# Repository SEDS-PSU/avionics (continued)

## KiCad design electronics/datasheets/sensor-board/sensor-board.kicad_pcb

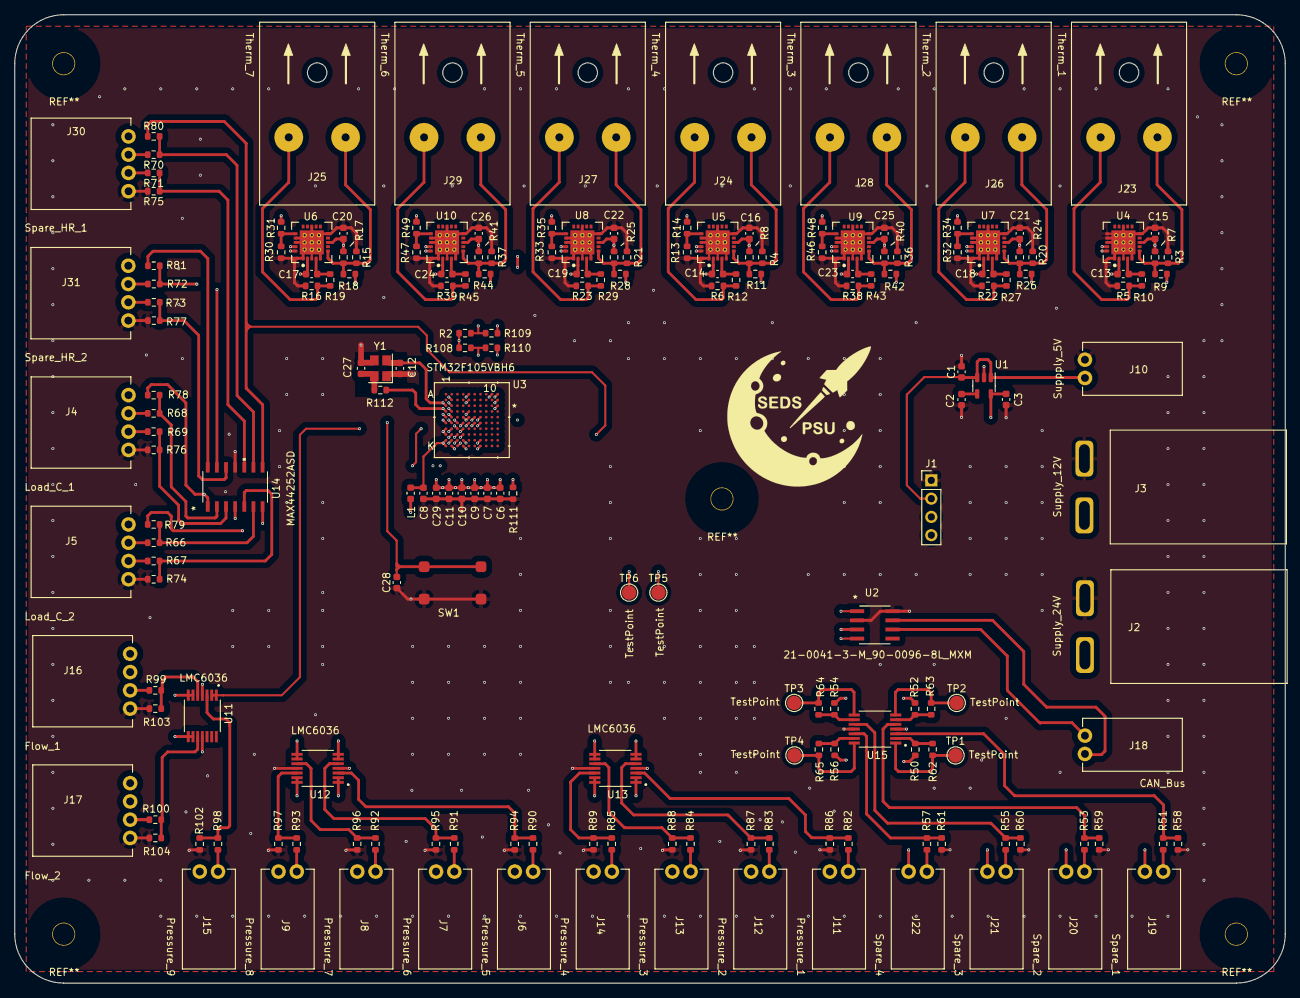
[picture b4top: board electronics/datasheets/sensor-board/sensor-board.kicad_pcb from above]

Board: 4 copper layers, 176.6 x 134.6 mm, 190 parts (0 on the bottom side), 131 nets.

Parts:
C1, C3: 1uF; C_0603_1608Metric
C2: 10nF; C_0603_1608Metric
C6, C7, C8, C9, C10, C11, C28, C29: 100nF; C_0603_1608Metric
C12, C27: 20pF; C_0603_1608Metric
C13, C14, C15, C16, C17, C18, C19, C20, C21, C22, C23, C24, C25, C26: 0.1uF; C_0603_1608Metric
J1: SWD Header; PinHeader_1x04_P2.54mm_Vertical
J2: Supply_24V; PowerPoleThroughHole
J3: Supply_12V; PowerPoleThroughHole
J4: Load_C_1; SL_2.54_H_4pin
J5: Load_C_2; SL_2.54_H_4pin
J6: Pressure_5; SL_2.54_H_2pin
J7: Pressure_6; SL_2.54_H_2pin
J8: Pressure_7; SL_2.54_H_2pin
J9: Pressure_8; SL_2.54_H_2pin
J10: Suppply_5V; SL_2.54_H_2pin
J11: Pressure_1; SL_2.54_H_2pin
J12: Pressure_2; SL_2.54_H_2pin
J13: Pressure_3; SL_2.54_H_2pin
J14: Pressure_4; SL_2.54_H_2pin
J15: Pressure_9; SL_2.54_H_2pin
J16: Flow_1; SL_2.54_H_4pin
J17: Flow_2; SL_2.54_H_4pin
J18: CAN_Bus; SL_2.54_H_2pin
J19: Spare_1; SL_2.54_H_2pin
J20: Spare_2; SL_2.54_H_2pin
J21: Spare_3; SL_2.54_H_2pin
J22: Spare_4; SL_2.54_H_2pin
J23: Therm_1; K_type_thermo_conn_F
J24: Therm_4; K_type_thermo_conn_F
J25: Therm_7; K_type_thermo_conn_F
J26: Therm_2; K_type_thermo_conn_F
J27: Therm_5; K_type_thermo_conn_F
J28: Therm_3; K_type_thermo_conn_F
J29: Therm_6; K_type_thermo_conn_F
J30: Spare_HR_1; SL_2.54_H_4pin
J31: Spare_HR_2; SL_2.54_H_4pin
L1: 10uH; L_0603_1608Metric
R2, R108: 4.7k; R_0603_1608Metric
R3, R4, R5, R6, R15, R16, R20, R21, R22, R23, R36, R37, R38, R39: 2M; R_0603_1608Metric
R7, R8, R17, R24, R25, R40, R41: 1M; R_0603_1608Metric
R9, R10, R11, R12, R18, R19, R26, R27, R28, R29, R42, R43, R44, R45, R66, R68, R70, R72, R109, R110: 100; R_0603_1608Metric
R13, R30, R32, R33, R46, R47, R111: 10k; R_0603_1608Metric
R14: 7.5k; R_0603_1608Metric
R31: 43k; R_0603_1608Metric
R34: 2.2k; R_0603_1608Metric
R35: 13k; R_0603_1608Metric
R48: 4.3k; R_0603_1608Metric
R49: 22k; R_0603_1608Metric
R50, R51, R52, R53, R54, R55, R56, R57, R58, R59, R60, R61, R62, R63, R64, R65: NO_RES; R_0603_1608Metric
R67, R69, R71, R73: 24.92; R_0603_1608Metric
R74, R75, R76, R77, R78, R79, R80, R81: 82500; R_0603_1608Metric
R82, R83, R84, R85, R86, R87, R88, R89, R90, R91, R92, R93, R94, R95, R96, R97, R98, R99, R100, R102, R103, R104: 150; R_0603_1608Metric
R112: 0k; R_0603_1608Metric
Ref**: Val**; seds-logo
SW1: SW_Push_Dual; Button CS1102
TP1, TP2, TP3, TP4, TP5, TP6: TestPoint; TestPoint_Pad_D2.0mm
U1: LD3985M33R_SOT23; SOT-23-5
U2: 21-0041-3-M_90-0096-8L_MXM; MAX33012EASA+
U3: STM32F105VBH6
U4, U5, U6, U7, U8, U9, U10: MCP96RL01T; MCP96RL01T_QFN
U11, U12, U13, U15: LMC6036; SOP65P640X120-14N
U14: MAX44252ASD; MAX44252ASD&plus_
Y1: Crystal_GND24; Crystal_SMD_3225-4Pin_3.2x2.5mm

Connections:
+3V3: C3.1, C6.1, C7.1, C9.1, C10.1, C11.1, C15.1, C16.1, C20.1, C21.1, C22.1, C25.1, C26.1, C29.1, L1.2, R2.1, R7.1, R8.1, R14.2, R17.1, R24.1, R25.1, R31.2, R34.2, R35.2, R40.1, R41.1, R48.2, R49.2, R108.1, U1.5 (VOUT), U2.3 (VDD), U3.B2 (VBAT), U3.D2 (VDD_5), U3.F4 (VDD_4), U3.F5 (VDD_3), U3.F6 (VDD_2), U3.F7 (VDD_1), U4.8 (VDD), U5.8 (VDD), U6.8 (VDD), U7.8 (VDD), U8.8 (VDD), U9.8 (VDD), U10.8 (VDD), U11.4 (VDD), U12.4 (VDD), U13.4 (VDD), U14.4 (VDD), U15.4 (VDD)
+5V: C1.1, J1.2, J10.1, U1.1 (VIN), U1.3 (INH)
+12V: J3.1, J4.1, J5.1, J6.1, J7.1, J8.1, J9.1, J11.1, J12.1, J13.1, J14.1, J15.1, J30.1, J31.1
+24V: J2.1, J16.1, J17.1
/ADC12_IN0: R78.1, U3.G2 (PA0-WKUP), U14.1 (OUTA)
/ADC12_IN1: R79.1, U3.H2 (PA1), U14.7 (OUTB)
/ADC12_IN2: U3.J2 (PA2), U12.8 (OUTC), U12.9 (INC-)
/ADC12_IN3: U3.K2 (PA3), U12.13 (IND-), U12.14 (OUTD)
/ADC12_IN4: U3.G3 (PA4), U12.1 (OUTA), U12.2 (INA-)
/ADC12_IN5: U3.H3 (PA5), U12.6 (INB-), U12.7 (OUTB)
/ADC12_IN6: U3.J3 (PA6), U13.1 (OUTA), U13.2 (INA-)
/ADC12_IN7: U3.K3 (PA7), U13.6 (INB-), U13.7 (OUTB)
/ADC12_IN8: U3.J4 (PB0), U13.8 (OUTC), U13.9 (INC-)
/ADC12_IN9: U3.K4 (PB1), U13.13 (IND-), U13.14 (OUTD)
/ADC12_IN10: U3.F1 (PC0), U11.1 (OUTA), U11.2 (INA-)
/ADC12_IN11: U3.F2 (PC1), U11.6 (INB-), U11.7 (OUTB)
/ADC12_IN12: U3.E2 (PC2), U11.8 (OUTC), U11.9 (INC-)
/ADC12_IN13: TP5.1, U3.F3 (PC3)
/ADC12_IN14: TP6.1, U3.G4 (PC4)
/ADC12_IN15: R80.1, U3.H4 (PC5), U14.8 (OUTC)
/CAN_RX: U2.4 (RXD), U3.C10 (PA11)
/CAN_TX: U2.1 (TXD), U3.B10 (PA12)
/I2C1_SCL: R2.2, R109.1, U4.19 (SCL), U5.19 (SCL), U6.19 (SCL), U7.19 (SCL), U8.19 (SCL), U9.19 (SCL), U10.19 (SCL)
/I2C1_SDA: R108.2, R110.1, U4.20 (SDA), U5.20 (SDA), U6.20 (SDA), U7.20 (SDA), U8.20 (SDA), U9.20 (SDA), U10.20 (SDA)
/Load Cell/diff+A: J4.3, R69.2
/Load Cell/diff+B: J5.3, R67.2
/Load Cell/diff+C: J30.3, R71.2
/Load Cell/diff+D: J31.3, R73.2
/Load Cell/diff-A: J4.2, R68.2
/Load Cell/diff-B: J5.2, R66.2
/Load Cell/diff-C: J30.2, R70.2
/Load Cell/diff-D: J31.2, R72.2
/Load Cell/output_D: R81.1, U14.14 (OUTD)
/Pressure 1/diff+A: J11.2, R82.2
/Pressure 1/diff+B: J12.2, R83.2
/Pressure 1/diff+C: J13.2, R84.2
/Pressure 1/diff+D: J14.2, R85.2
/Pressure 2/diff+A: J6.2, R90.2
/Pressure 2/diff+B: J7.2, R91.2
/Pressure 2/diff+C: J8.2, R92.2
/Pressure 2/diff+D: J9.2, R93.2
/Pressure and Flow/diff+A: J15.2, R98.2
/Pressure and Flow/diff+B: J16.3, R99.2
/Pressure and Flow/diff+C: J17.3, R100.2
/SPARE_gen_purp_amp/diff+A: J19.2, R51.2
/SPARE_gen_purp_amp/diff+B: J20.2, R53.2
/SPARE_gen_purp_amp/diff+C: J21.2, R55.2
/SPARE_gen_purp_amp/diff+D: J22.2, R57.2
/SPARE_gen_purp_amp/diff-A: J19.1, R50.2
/SPARE_gen_purp_amp/diff-B: J20.1, R52.2
/SPARE_gen_purp_amp/diff-C: J21.1, R54.2
/SPARE_gen_purp_amp/diff-D: J22.1, R56.2
/SPARE_gen_purp_amp/output_A: R62.1, TP1.1, U15.1 (OUTA)
/SPARE_gen_purp_amp/output_B: R63.1, TP2.1, U15.7 (OUTB)
/SPARE_gen_purp_amp/output_C: R64.1, TP3.1, U15.8 (OUTC)
/SPARE_gen_purp_amp/output_D: R65.1, TP4.1, U15.14 (OUTD)
/SWCLK: J1.3, U3.A9 (PA14)
/SWDIO: J1.4, U3.A10 (PA13)
GND: C1.2, C2.2, C3.2, C6.2, C7.2, C8.2, C9.2, C10.2, C11.2, C12.1, C15.2, C16.2, C20.2, C21.2, C22.2, C25.2, C26.2, C27.1, C28.1, C29.2, J1.1, J2.2, J3.2, J4.4, J5.4, J10.2, J16.4, J17.4, J30.4, J31.4, R3.2, R4.2, R5.2, R6.2, R13.2, R15.2, R16.2, R20.2, R21.2, R22.2, R23.2, R30.2, R32.2, R33.2, R36.2, R37.2, R38.2, R39.2, R46.2, R47.2, R58.2, R59.2, R60.2, R61.2, R74.2, R75.2, R76.2, R77.2, R86.2, R87.2, R88.2, R89.2, R94.2, R95.2, R96.2, R97.2, R102.2, R103.2, R104.2, R111.2, SW1.1, SW1.3, U1.2 (GND), U2.2 (GND), U2.8 (STBY), U3.C2 (VSS_5), U3.E4 (VSS_4), U3.E5 (VSS_3), U3.E6 (VSS_2), U3.E7 (VSS_1), U3.G1 (VSSA), U3.H1 (VREF-), U4.1 (GND), U4.3 (GND), U4.5 (GND), U4.10 (GND), U4.13 (GND), U4.16 (ADDR), U4.17 (GND), U4.18 (GND), U4.21 (Body_(gnd)), U5.1 (GND), U5.3 (GND), U5.5 (GND), U5.10 (GND), U5.13 (GND), U5.17 (GND), U5.18 (GND), U5.21 (Body_(gnd)), U6.1 (GND), U6.3 (GND), U6.5 (GND), U6.10 (GND), U6.13 (GND), U6.17 (GND), U6.18 (GND), U6.21 (Body_(gnd)), U7.1 (GND), U7.3 (GND), U7.5 (GND), U7.10 (GND), U7.13 (GND), U7.17 (GND), U7.18 (GND), U7.21 (Body_(gnd)), U8.1 (GND), U8.3 (GND), U8.5 (GND), U8.10 (GND), U8.13 (GND), U8.17 (GND), U8.18 (GND), U8.21 (Body_(gnd)), U9.1 (GND), U9.3 (GND), U9.5 (GND), U9.10 (GND), U9.13 (GND), U9.17 (GND), U9.18 (GND), U9.21 (Body_(gnd)), U10.1 (GND), U10.3 (GND), U10.5 (GND), U10.10 (GND), U10.13 (GND), U10.17 (GND), U10.18 (GND), U10.21 (Body_(gnd)), U11.11 (VSS), U12.11 (VSS), U13.11 (VSS), U14.11 (VSS), U15.11 (VSS), Y1.1, Y1.3
unnamed: C2.1, U1.4 (BYP)
unnamed: C12.2, U3.C1 (OSC_IN), Y1.2
unnamed: C13.1, R9.2, U4.2 (VIN+)
unnamed: C13.2, R10.2, U4.4 (VIN-)
unnamed: C14.1, R11.2, U5.2 (VIN+)
unnamed: C14.2, R12.2, U5.4 (VIN-)
unnamed: C17.1, R18.2, U6.2 (VIN+)
unnamed: C17.2, R19.2, U6.4 (VIN-)
unnamed: C18.1, R26.2, U7.2 (VIN+)
unnamed: C18.2, R27.2, U7.4 (VIN-)
unnamed: C19.1, R28.2, U8.2 (VIN+)
unnamed: C19.2, R29.2, U8.4 (VIN-)
unnamed: C23.1, R42.2, U9.2 (VIN+)
unnamed: C23.2, R43.2, U9.4 (VIN-)
unnamed: C24.1, R44.2, U10.2 (VIN+)
unnamed: C24.2, R45.2, U10.4 (VIN-)
unnamed: C27.2, R112.1, Y1.4
unnamed: C28.2, SW1.2, SW1.4, U3.E1 (NRST)
unnamed: J18.1, U2.7 (CANH)
unnamed: J18.2, U2.6 (CANL)
unnamed: J23.1, R3.1, R7.2, R9.1, U4.6 (VSENSE)
unnamed: J23.2, R5.1, R10.1
unnamed: J24.1, R4.1, R8.2, R11.1, U5.6 (VSENSE)
unnamed: J24.2, R6.1, R12.1
unnamed: J25.1, R15.1, R17.2, R18.1, U6.6 (VSENSE)
unnamed: J25.2, R16.1, R19.1
unnamed: J26.1, R20.1, R24.2, R26.1, U7.6 (VSENSE)
unnamed: J26.2, R22.1, R27.1
unnamed: J27.1, R21.1, R25.2, R28.1, U8.6 (VSENSE)
unnamed: J27.2, R23.1, R29.1
unnamed: J28.1, R36.1, R40.2, R42.1, U9.6 (VSENSE)
unnamed: J28.2, R38.1, R43.1
unnamed: J29.1, R37.1, R41.2, R44.1, U10.6 (VSENSE)
unnamed: J29.2, R39.1, R45.1
unnamed: R13.1, R14.1, U5.16 (ADDR)
unnamed: R30.1, R31.1, U6.16 (ADDR)
unnamed: R32.1, R34.1, U7.16 (ADDR)
unnamed: R33.1, R35.1, U8.16 (ADDR)
unnamed: R46.1, R48.1, U9.16 (ADDR)
unnamed: R47.1, R49.1, U10.16 (ADDR)
unnamed: R50.1, R62.2, U15.2 (INA-)
unnamed: R51.1, R58.1, U15.3 (INA+)
unnamed: R52.1, R63.2, U15.6 (INB-)
unnamed: R53.1, R59.1, U15.5 (INB+)
unnamed: R54.1, R64.2, U15.9 (INC-)
unnamed: R55.1, R60.1, U15.10 (INC+)
unnamed: R56.1, R65.2, U15.13 (IND-)
unnamed: R57.1, R61.1, U15.12 (IND+)
unnamed: R66.1, R79.2, U14.6 (INB-)
unnamed: R67.1, R74.1, U14.5 (INB+)
unnamed: R68.1, R78.2, U14.2 (INA-)
unnamed: R69.1, R76.1, U14.3 (INA+)
unnamed: R70.1, R80.2, U14.9 (INC-)
unnamed: R71.1, R75.1, U14.10 (INC+)
unnamed: R72.1, R81.2, U14.13 (IND-)
unnamed: R73.1, R77.1, U14.12 (IND+)
unnamed: R82.1, R86.1, U13.3 (INA+)
unnamed: R83.1, R87.1, U13.5 (INB+)
unnamed: R84.1, R88.1, U13.10 (INC+)
unnamed: R85.1, R89.1, U13.12 (IND+)
unnamed: R90.1, R94.1, U12.3 (INA+)
unnamed: R91.1, R95.1, U12.5 (INB+)
unnamed: R92.1, R96.1, U12.10 (INC+)
unnamed: R93.1, R97.1, U12.12 (IND+)
unnamed: R100.1, R104.1, U11.10 (INC+)
unnamed: R98.1, R102.1, U11.3 (INA+)
unnamed: R99.1, R103.1, U11.5 (INB+)
unnamed: R109.2, U3.B5 (PB6)
unnamed: R110.2, U3.A5 (PB7)
unnamed: R111.1, U3.D5 (BOOT0)
unnamed: R112.2, U3.D1 (OSC_OUT)
VDDA: C8.1, L1.1, U3.J1 (VREF+), U3.K1 (VDDA)

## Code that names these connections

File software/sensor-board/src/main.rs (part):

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        adc::{Adc, SampleTime},
        can::Can,
        gpio::{
            gpioa::{PA0, PA1, PA2, PA3, PA4, PA5, PA6, PA7},
            gpiob::{PB0, PB1, PB6, PB7},
            gpioc::{PC0, PC1, PC2},
            Alternate, Analog, OpenDrain, PushPull, Output, Input, Floating, PC4,
        },
        i2c::BlockingI2c,
        pac::{Interrupt, ADC1, CAN1, I2C1, TIM1, TIM2},
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    #[monotonic(binds = TIM2, default = true)]
    type Mono = MonoTimerUs<TIM2>;

    type I2c1 = BlockingI2c<I2C1, (PB6<Alternate<OpenDrain>>, PB7<Alternate<OpenDrain>>)>;
    type I2c1Proxy = shared_bus::I2cProxy<'static, shared_bus::AtomicCheckMutex<I2c1>>;

    pub struct AnalogPins {
        // load_cell1: PA0<Analog>,
        // load_cell2: PA1<Analog>,

        pressure1: PA6<Analog>,
        pressure2: PA7<Analog>,
        pressure3: PB0<Analog>,
        pressure4: PB1<Analog>,
        pressure5: PA4<Analog>,
        pressure6: PA5<Analog>,
        pressure7: PA2<Analog>,
        pressure8: PA3<Analog>,
        pressure9: PC0<Analog>,

        flow1: PC1<Analog>,
        flow2: PC2<Analog>,

        // battery: PC3<Analog>, // Assignment may change.
    }

    pub struct Thermocouples {
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        thermocouples: Thermocouples,
        dual_hx711: Option<DualHx711<
            DelayUs<TIM1>,
            PA0<Input<Floating>>,
            PA1<Input<Floating>>,
            PC4<Output<PushPull>>,
        >>,
    }

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        let mut gpioc = cx.device.GPIOC.split();

        let analog_pins = AnalogPins {
            pressure1: gpioa.pa6.into_analog(&mut gpioa.crl),
            pressure2: gpioa.pa7.into_analog(&mut gpioa.crl),
            pressure3: gpiob.pb0.into_analog(&mut gpiob.crl),
            pressure4: gpiob.pb1.into_analog(&mut gpiob.crl),
            pressure5: gpioa.pa4.into_analog(&mut gpioa.crl),
            pressure6: gpioa.pa5.into_analog(&mut gpioa.crl),
            pressure7: gpioa.pa2.into_analog(&mut gpioa.crl),
            pressure8: gpioa.pa3.into_analog(&mut gpioa.crl),
            pressure9: gpioc.pc0.into_analog(&mut gpioc.crl),

            flow1: gpioc.pc1.into_analog(&mut gpioc.crl),
            flow2: gpioc.pc2.into_analog(&mut gpioc.crl),

            // battery: gpioc.pc3.into_analog(&mut gpioc.crl),
        };

        let mut dwt = cx.core.DWT;
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        dwt.enable_cycle_counter();

        let bus_manager: &'static _ = {
            let i2c_scl = gpiob.pb6.into_alternate_open_drain(&mut gpiob.crl);
            let i2c_sda = gpiob.pb7.into_alternate_open_drain(&mut gpiob.crl);

            let i2c1 = BlockingI2c::i2c1(
                cx.device.I2C1,
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
        let mut dual_hx711 = DualHx711::new(
            delay,
            gpioa.pa0.into_floating_input(&mut gpioa.crl),
            gpioa.pa1.into_floating_input(&mut gpioa.crl),
            gpioc.pc4.into_push_pull_output(&mut gpioc.crl),
            Hx711Mode::ChAGain128,
        ).map_err(|e| {
            defmt::error!("failed to initialize dual HX711: {:?}", e);
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            dual_hx711.set_scale(hx711::FP::from_num(6284) / 100, hx711::FP::from_num(1) /* unknown currently */);
        }

        let can_rx_pin = gpioa.pa11.into_floating_input(&mut gpioa.crh);
        let can_tx_pin = gpioa.pa12.into_alternate_push_pull(&mut gpioa.crh);

        can.assign_pins((can_tx_pin, can_rx_pin), &mut afio.mapr);

        // APB1 (PCLK1): 9MHz, Bit rate: 500kBit/s, Sample Point 87.5%
        // Value was calculated with http://www.bittiming.can-wiki.info/
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
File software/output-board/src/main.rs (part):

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    use stm32f1xx_hal::{
        can::Can,
        gpio::{
            gpiob::{PB0, PB1, PB10, PB11, PB12, PB15, PB2, PB3, PB4, PB5, PB6, PB7, PB8, PB9},
            gpiod::PD12,
            Edge, ExtiPin, Input, Output, PinState, PullDown, PushPull,
        },
        pac::{Interrupt, CAN1},
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    }

    pub struct ActuationPins {
        solenoid1: PB1<Output<PushPull>>,
        solenoid2: PB2<Output<PushPull>>,
        solenoid3: PB3<Output<PushPull>>,
        solenoid4: PB4<Output<PushPull>>,
        solenoid5: PB5<Output<PushPull>>,
        solenoid6: PB6<Output<PushPull>>,
        solenoid7: PB7<Output<PushPull>>,
        solenoid8: PB0<Output<PushPull>>,
        solenoid9: PB8<Output<PushPull>>,
        solenoid10: PB9<Output<PushPull>>,

        // These are walled-off by the arming mosfet.
        main_fuel_solenoid: PB10<Output<PushPull>>,
        main_oxidizer_solenoid: PB11<Output<PushPull>>,
    }

    // Shared resources go here
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        /// at a time, but it's a good idea to have a small slack.
        can_tx_queue: Queue<Frame, 4>,

        arming_switch: PB15<Input<PullDown>>,
        ignition_detection: PD12<Input<PullDown>>,

        /// The `#[lock_free]` attribute makes sure that access to this
        /// is always deterministic (since only tasks at a single priority
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        actuation_pins: ActuationPins,

        /// This is walled-off by the arming mosfet.
        igniter_pin: PB12<Output<PushPull>>,
    }

    #[init(local = [command_list: Deque<pi_output::Command, 256> = Deque::new()])]
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        let mut gpiob = cx.device.GPIOB.split();
        let mut gpiod = cx.device.GPIOD.split();

        // The pb3 and pb4 pins are used by the JTAG debugger initially.
        // We need to disable the JTAG peripheral to use them.
        let (_, pb3, pb4) = afio.mapr.disable_jtag(gpioa.pa15, gpiob.pb3, gpiob.pb4);

        let actuation_pins = ActuationPins {
            solenoid1: gpiob.pb1.into_push_pull_output(&mut gpiob.crl),
            solenoid2: gpiob.pb2.into_push_pull_output(&mut gpiob.crl),
            solenoid3: pb3.into_push_pull_output(&mut gpiob.crl),
            solenoid4: pb4.into_push_pull_output(&mut gpiob.crl),
            solenoid5: gpiob.pb5.into_push_pull_output(&mut gpiob.crl),
            solenoid6: gpiob.pb6.into_push_pull_output(&mut gpiob.crl),
            solenoid7: gpiob.pb7.into_push_pull_output(&mut gpiob.crl),
            solenoid8: gpiob.pb0.into_push_pull_output(&mut gpiob.crl),
            solenoid9: gpiob.pb8.into_push_pull_output(&mut gpiob.crh),
            solenoid10: gpiob.pb9.into_push_pull_output(&mut gpiob.crh),
            main_fuel_solenoid: gpiob.pb10.into_push_pull_output(&mut gpiob.crh),
            main_oxidizer_solenoid: gpiob.pb11.into_push_pull_output(&mut gpiob.crh),
        };

        let igniter_pin = gpiob.pb12.into_push_pull_output(&mut gpiob.crh);

        let arming_switch = gpiob.pb15.into_pull_down_input(&mut gpiob.crh);
        let mut ignition_detection = gpiod.pd12.into_pull_down_input(&mut gpiod.crh);

        // Set up the ignition detection interrupt handler.
        // This will trigger on EXTI1.
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        ignition_detection.enable_interrupt(&mut exti);
        ignition_detection.trigger_on_edge(&mut exti, Edge::Falling);

        let can_rx_pin = gpioa.pa11.into_floating_input(&mut gpioa.crh);
        let can_tx_pin = gpioa.pa12.into_alternate_push_pull(&mut gpioa.crh);

        can.assign_pins((can_tx_pin, can_rx_pin), &mut afio.mapr);

        // APB1 (PCLK1): 9MHz, Bit rate: 500kBit/s, Sample Point 87.5%
        // Value was calculated with http://www.bittiming.can-wiki.info/
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
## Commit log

2021-09-18 Change to general avionics repo
2021-09-18 Add kicad projects
2021-09-18 Remove left over files
2021-09-18 Add new open files
2021-09-18 Remove output-io
2021-09-18 Added title to sensor board
2021-09-18 Add MAX33012EASA+ component to electronics/libraries/
2021-09-18 Added library for BSS806N MOSFET
2021-09-18 Ignore .DS_store
2021-09-18 Added ADC KiCAD library
2021-09-18 Added STM32 library
2021-09-18 Fixed library directory in sensor board schematic
2021-09-18 Add components necessary for raspi hat
2021-09-18 Added libraries to sensor board pcb schematic
2021-09-18 Added BSS806N library to the output board
2021-09-18 Added libraries to sensor board schematics
2021-09-18 STM32 and ADC datasheets added
2021-09-18 started working on output board
2021-09-18 Add initial library for ADS114S08 ADC
2021-09-20 Add read function to ADS114S08 driver
2021-09-21 Moved stm32 datasheet in appropriate folder
2021-09-21 Schematic edit
2021-09-21 Add mcu-base
2021-09-21 Sensor board schematic modified
2021-09-21 Add regulator and CAN transceiver to mcu-base
2021-09-21 Remove mcu-base hiearchical sheet from sensor-board
2021-09-21 Replaced sensor-board with nicholas' changes
2021-09-21 Put all analog outputs on a bus
2021-09-22 Add oscillators and some various stuff around the stm32 to the mcu-base
2021-09-23 Remove hiearchy from mcu-base
2021-09-28 Copied mcu-base schematic into sensor-board
2021-09-28 Update mcu base
2021-09-28 Added MOSFETS to the output board.
2021-10-05 Add sensor board starting code
2021-10-06 Added Op Amp Library to sensor-board
2021-10-12 added datasheet, modified sensor-board schematic
2021-10-12 edited sensor-board
2021-10-15 Switched Op Amps
    Added library files for both op amps (precision and general purpose)
    Couldn't find symbol library for gen-purp. op amp
2021-10-16 Custom MAX44252 symbol created
2021-10-16 sensor-board edit, base differential amp. laid out
2021-10-17 Finished Schematic and Started Routing the Output Board
2021-10-19 Working on ouput board.
    Saving before using the replicate layout plugin.
2021-10-19 sensor-board layout edit
    op amp subunits added
2021-10-25 sensor-board edit
2021-10-26 Output Board is basically done!
2021-10-26 sensor-board edits
    Finalized pressure and flow sensor circuits.
    Reorganized schematics
2021-11-03 added datasheets
2021-11-05 Start documenting the example software.
2021-11-06 work on sensor-board
    added MCP960 footprint
    finished MCP960 array schematic
2021-11-06 work on sensor-board
    thermocouple connector footprints made (selected connector)
2021-11-06 Finish adding documentation o the rtic sensor-board example.
2021-11-09 Put in connectors and finalized layout of everything except MCU.
2021-11-10 work on sensor-board
    finishing sub-circuits
    switching mcu to stm32f105
2021-11-10 Finalized sensor-board schematic
2021-11-10 Updated MCU Base and started MCU on Output Board
2021-11-16 Add MYSGK02506BRSR and start adding MYMGA5R04RELA5RA to Raspi HAT
2021-11-16 Continued Laying Out Output Board
2021-11-18 Finish adding MYMGA5R04RELA5RA
2021-11-18 continued working on four-layer output board
2021-11-18 Working on Output Board
2021-11-22 finished (mostly) output board
2021-11-25 Start laying out PCB for raspberry pi hat
2021-11-27 work on sensor-board
2021-11-28 work on sensor-board pcb
2021-11-28 Minor routing changes
2021-12-01 minor changes to output board
2021-12-02 added power leds and ignition detection
2022-01-02 Finish designing raspi hat
2022-01-02 Add SEDS logo to raspberry pi hat
2022-01-02 Fix footprint paths and add SEDS logo to output board
2022-01-02 Add SEDS logo to sensor board
2022-01-05 Start working on shared crate for test-stand software
2022-01-09 Add filled backplane to raspberry pi hat
2022-01-11 Finished sensor-board
2022-01-11 Edit to sensor-board
2022-01-13 Boards sent off to get fabricated
2022-01-13 Increase the size of a couple of vias on the output board
2022-01-18 Add existing files for the RPi controller software proof-of-concept
2022-01-19 Created BOM
2022-01-19 added thermocouple connector link
2022-01-19 Add sensor-board boilerplate and set-up code
2022-01-19 Update shared to match the decided communication protocols between raspberry pi and boards
2022-01-19 BOM update
2022-01-20 Add all sensors to shared crate
2022-01-21 Output board additions
2022-01-21 Do a lot more work on communications for the output board
2022-01-21 Add a bit of internal documentation
2022-01-21 Fix incorrect queue length
2022-01-22 Add support for arming and ignition detection
2022-01-23 testing bash git
2022-01-24 Do a bunch more work on the output-board software
2022-01-25 Add ignition detection and run cargo fmt
2022-01-26 Fix ignition detection
2022-01-27 Get output board software much closer to ready
2022-01-29 Add sensor names to shared library
2022-01-29 Output board code is ready for testing
2022-01-29 Bind CAN pins
2022-01-31 Port communications formatting over to postcard
2022-01-31 Add initial driver implementation for the MCP96X thermocouple ICs
2022-01-31 Get sensor board software into a state from which testing can begin
2022-01-31 Set defmt to always log at the info level or lower
2022-01-31 Change sensor type for load cells to Force
2022-02-06 Change sysclk to 25 MHz
2022-02-07 Start getting I2C driver working
2022-02-07 Added test cases for output board
2022-02-07 Attempt to get sensor board communicating with the thermocouple ICs
2022-02-11 Allow for partial thermocouple set initialization
2022-02-14 Keep working on getting thermocouples to work
2022-02-19 Add manual conversion to celsius for the thermocouple IC
2022-02-21 resistor values fixed in sensor-board
2022-02-21 Start implementing valve sequences and valve sequence change commands for Pi controller demo
2022-02-21 Started updating the output board
2022-02-24 Revising Output Board
2022-02-24 More output board revisions
2022-02-26 Implement proof-of-concept for sending valve sequence commands to the output board
2022-02-26 Start creating mock of output board
2022-02-27 Update raspi HAT schematic
2022-02-28 Testing output board
2022-02-28 Add initial template pi binary software
2022-02-28 Add battery voltage reading to sensor board code
2022-03-01 Add some ground station comms stuff to the pi software
2022-03-03 Finishing touches on output board rev 2
2022-03-08 More work on sensor-board
2022-03-15 changed can transciever
2022-03-15 New transceiver on output board
2022-03-19 Moved Diodes closer to connectors
2022-03-20 Update Raspberry Pi HAT to Rev 2 requirements
2022-03-20 Re-add SEDS logo to Raspberry Pi HAT
2022-03-20 Updated CAN Transciever on sensor board
2022-03-20 Update HAT
2022-03-20 Fix unconnected items
2022-03-20 Fix DRC errors on Raspi HAT
2022-03-20 Fix battery voltage overflow bug
2022-03-21 updated loadcell amplifier
2022-03-23 almost final sensor-board pcb
2022-03-23 almost final sensor-board pcb 2
2022-03-23 more work on sensor-board pcb
2022-03-27 Hole Location File Added
2022-03-27 Added Hole Location Schematic
2022-03-27 work on BOM file
2022-03-27 Added hole locations for output-board
2022-03-30 updated bom excel file
2022-03-30 update on BOM
2022-04-13 res value fix
2022-04-16 Update embedded software for new board revisions
2022-04-16 Re-enable peripheral clock on sensor board
2022-04-16 Fix mcp96x temperature reading
2022-04-16 Possibly fix temperature reading
2022-04-16 --amend
2022-04-16 Thermocouples should work now
2022-04-16 Start updating pi software
2022-04-16 Increase sampling time on sensor board ADCs
2022-04-16 Disable frame queue on sensor board
2022-04-16 Remove testsuite from sensor board
2022-04-17 remove core affinities and fix deadline scheduling
2022-04-19 Fix output board CAN peripheral frequency, hopefully
2022-04-20 Started work on board mount
2022-04-20 The CAN bus works!
2022-04-21 Update output board software and the shared crate
2022-04-22 Update software for igniter-test
2022-04-24 Get sensor board software updated
2022-04-25 Maybe get sensor board comms working
2022-04-29 Update software for hot-fire
2022-04-30 Update software for cold-fire
2022-05-01 Update code after cold-flow
2022-05-02 Instrument sensor board tasks
2022-05-03 Untested rewrite of all embedded software
2022-05-03 Get communications in avionics system working
2022-05-03 Update for most recent sensor board changes
2022-05-05 Update everything for hot-fire electric boogaloo
